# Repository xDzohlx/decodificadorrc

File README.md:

# decodificadorrc
Decodificacor de radiocontrol

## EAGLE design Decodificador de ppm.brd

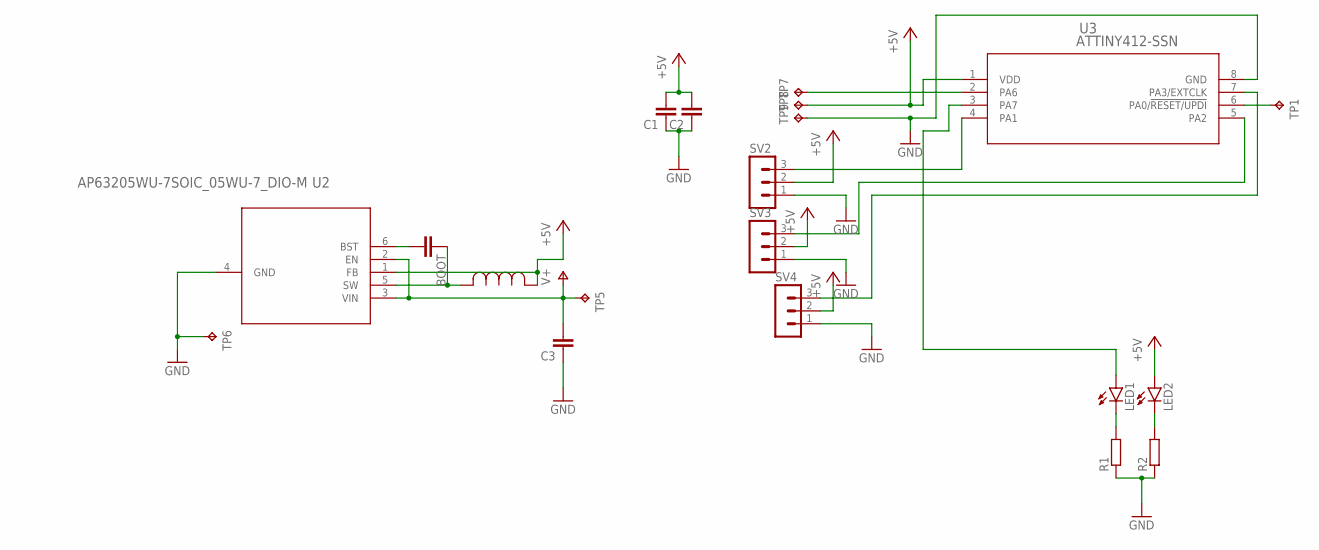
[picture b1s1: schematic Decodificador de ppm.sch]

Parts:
BOOT: C-EUC0402; C0402
C1, C2, C3: C-EUC0805; C0805
LED1, LED2: LEDCHIP-LED0603; CHIP-LED0603
R1, R2: R-EU_R0805; R0805
SV2, SV3, SV4: MA03-1
TP1: TPB1,27; B1,27
TP5, TP6, TP7, TP8, TP9: TPTP19SQ; TP19SQ
U2: AP63205WU-7SOIC_05WU-7_DIO-M; SOIC_05WU-7_DIO-M
U3: ATTINY412-SSN; SOIC8_SA_SST_MCH
U$2: INDUCTOR4.7; IND_NRS5030T100MMGJ_TAY

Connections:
+5V: C1.2, C2.2, LED2.A, SV2.2, SV3.2, SV4.2, TP8.TP, U2.1 (FB), U3.1 (VDD), U$2.1
GND: C1.1, C2.1, C3.1, R1.1, R2.1, SV2.1, SV3.1, SV4.1, TP6.TP, TP9.TP, U2.4 (GND), U3.8 (GND)
unnamed: LED1.C, R1.2
unnamed: LED2.C, R2.2
unnamed: TP7.TP, U3.2 (PA6)
unnamed: TP1.TP, U3.6 (PA0/!RESET/UPDI)
unnamed: SV2.3, U3.4 (PA1)
unnamed: SV3.3, U3.5 (PA2)
unnamed: SV4.3, U3.7 (PA3/EXTCLK)
unnamed: LED1.A, U3.3 (PA7)
unnamed: BOOT.1, U2.5 (SW), U$2.2
unnamed: BOOT.2, U2.6 (BST)
V+: C3.2, TP5.TP, U2.2 (EN), U2.3 (VIN)

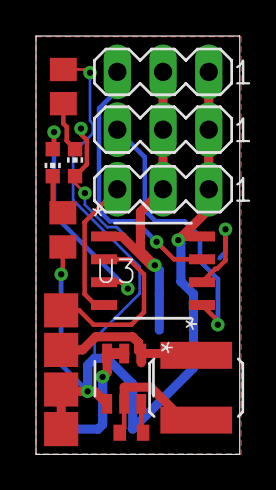
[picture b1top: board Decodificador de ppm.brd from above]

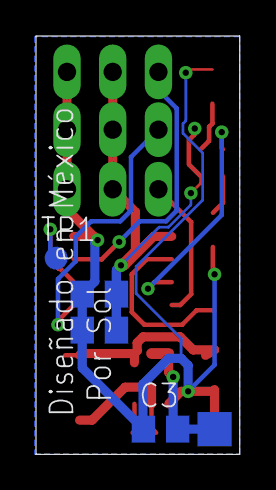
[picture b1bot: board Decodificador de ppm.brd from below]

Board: 2 copper layers, 11.3 x 23.2 mm, 20 parts (5 on the bottom side), 13 nets.

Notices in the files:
parts and their libraries:
COPYRIGHT: Copyright (C) 2018 Accelerated Designs. All rights reserved
